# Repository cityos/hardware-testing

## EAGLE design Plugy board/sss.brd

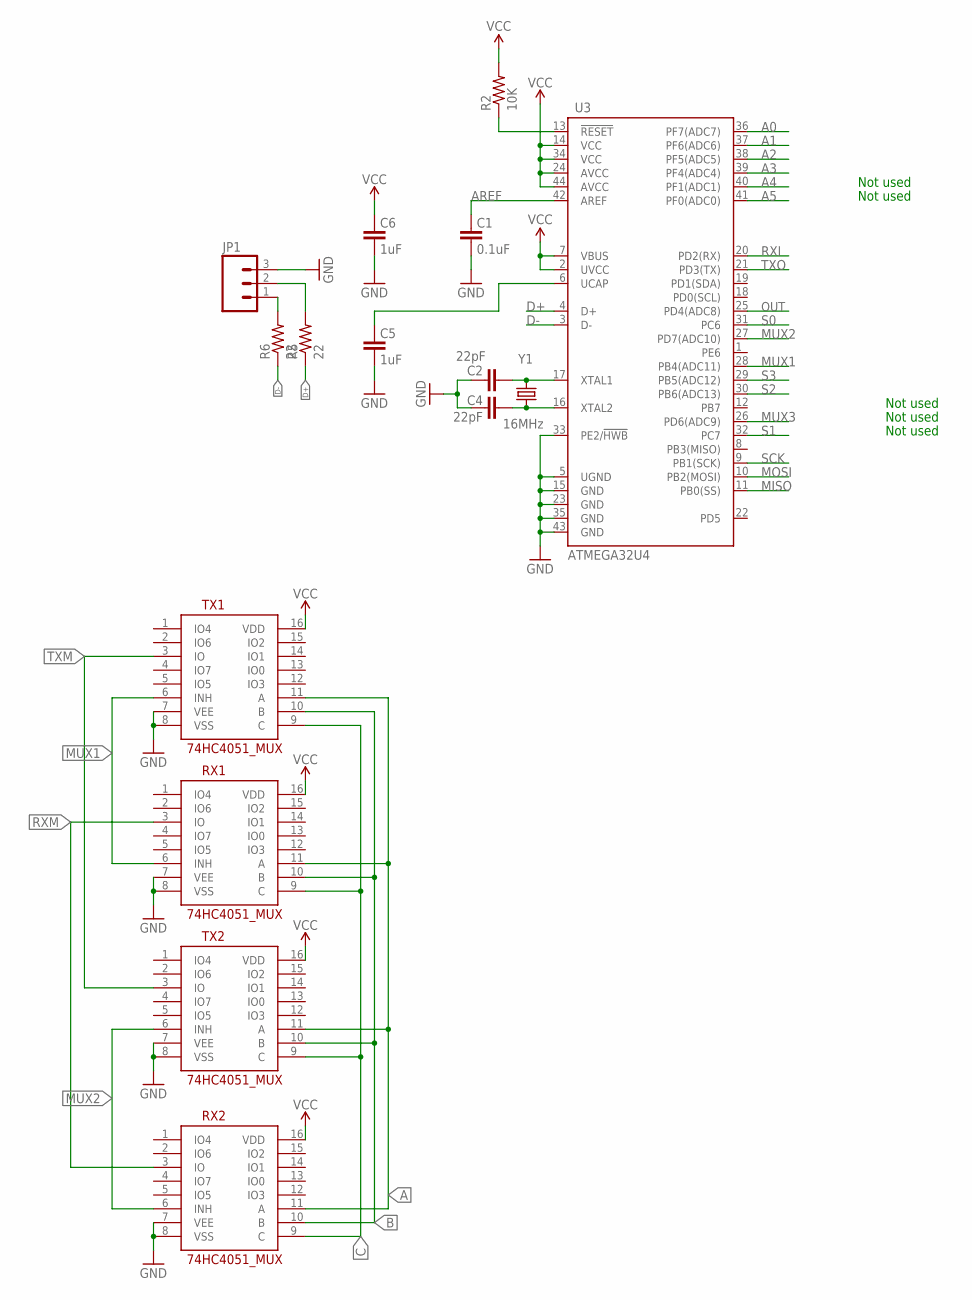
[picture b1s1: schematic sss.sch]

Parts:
C1: 0.1uF; 0603-CAP
C2, C4: 22pF; 0603-CAP
C5, C6: 1uF; 0603-CAP
JP1: M03PTH; 1X03
R2: 10K; 0603-RES
R5, R6: 22; 0603-RES
RX1, RX2: 74HC4051_MUX; SO16
TX1, TX2: 74HC4051_MUX; SO16
U3: ATMEGA32U4; QFN-44-NOPAD_1:1-OUTFAKES
Y1: 16MHz; CRYSTAL-SMD-5X3

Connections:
3.3V: C6.2, RX1.16 (VDD), RX2.16 (VDD), TX1.16 (VDD), TX2.16 (VDD)
A: RX1.11 (A), RX2.11 (A), TX1.11 (A), TX2.11 (A)
A0: U3.36 (PF7(ADC7))
A1: U3.37 (PF6(ADC6))
A2: U3.38 (PF5(ADC5))
A3: U3.39 (PF4(ADC4))
A4: U3.40 (PF1(ADC1))
A5: U3.41 (PF0(ADC0))
AREF: C1.2, U3.42 (AREF)
B: RX1.10 (B), RX2.10 (B), TX1.10 (B), TX2.10 (B)
C: RX1.9 (C), RX2.9 (C), TX1.9 (C), TX2.9 (C)
D+: R5.1, U3.4 (D+)
D-: R6.1, U3.3 (D-)
GND: C1.1, C2.2, C4.2, C5.1, C6.1, JP1.3, RX1.7 (VEE), RX1.8 (VSS), RX2.7 (VEE), RX2.8 (VSS), TX1.7 (VEE), TX1.8 (VSS), TX2.7 (VEE), TX2.8 (VSS), U3.5 (UGND), U3.15 (GND), U3.23 (GND), U3.33 (PE2/!HWB), U3.35 (GND), U3.43 (GND)
MISO: U3.11 (PB0(SS))
MOSI: U3.10 (PB2(MOSI))
MUX1: RX1.6 (INH), TX1.6 (INH), U3.28 (PB4(ADC11))
MUX2: RX2.6 (INH), TX2.6 (INH), U3.27 (PD7(ADC10))
MUX3: U3.26 (PD6(ADC9))
unnamed: C4.1, U3.16 (XTAL2), Y1.1
unnamed: C2.1, U3.17 (XTAL1), Y1.3 (2)
unnamed: C5.2, U3.6 (UCAP)
unnamed: JP1.1, R6.2
unnamed: JP1.2, R5.2
OUT: U3.25 (PD4(ADC8))
RESET: R2.1, U3.13 (!RESET)
RXI: U3.20 (PD2(RX))
RXM: RX1.3 (IO), RX2.3 (IO)
S0: U3.31 (PC6)
S1: U3.32 (PC7)
S2: U3.30 (PB6(ADC13))
S3: U3.29 (PB5(ADC12))
SCK: U3.9 (PB1(SCK))
TXM: TX1.3 (IO), TX2.3 (IO)
TXO: U3.21 (PD3(TX))
UVCC: U3.2 (UVCC), U3.7 (VBUS)
VCC: R2.2, U3.14 (VCC), U3.24 (AVCC), U3.34 (VCC), U3.44 (AVCC)

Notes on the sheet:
Not used

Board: 2 copper layers, 15 parts (10 on the bottom side), 20 nets, no tracks yet.

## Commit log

2016-07-18 added readme file
2016-07-18 add first code
2016-07-18 deleted dome line of code
2016-07-18 deleted code
2016-07-20 dodao pcb fajlove

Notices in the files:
parts and their libraries:
SparkFun-AnalogIC: Licensing:Creative Commons ShareAlike 4.0 International - https://creativecommons.org/licenses/by-sa/4.0
